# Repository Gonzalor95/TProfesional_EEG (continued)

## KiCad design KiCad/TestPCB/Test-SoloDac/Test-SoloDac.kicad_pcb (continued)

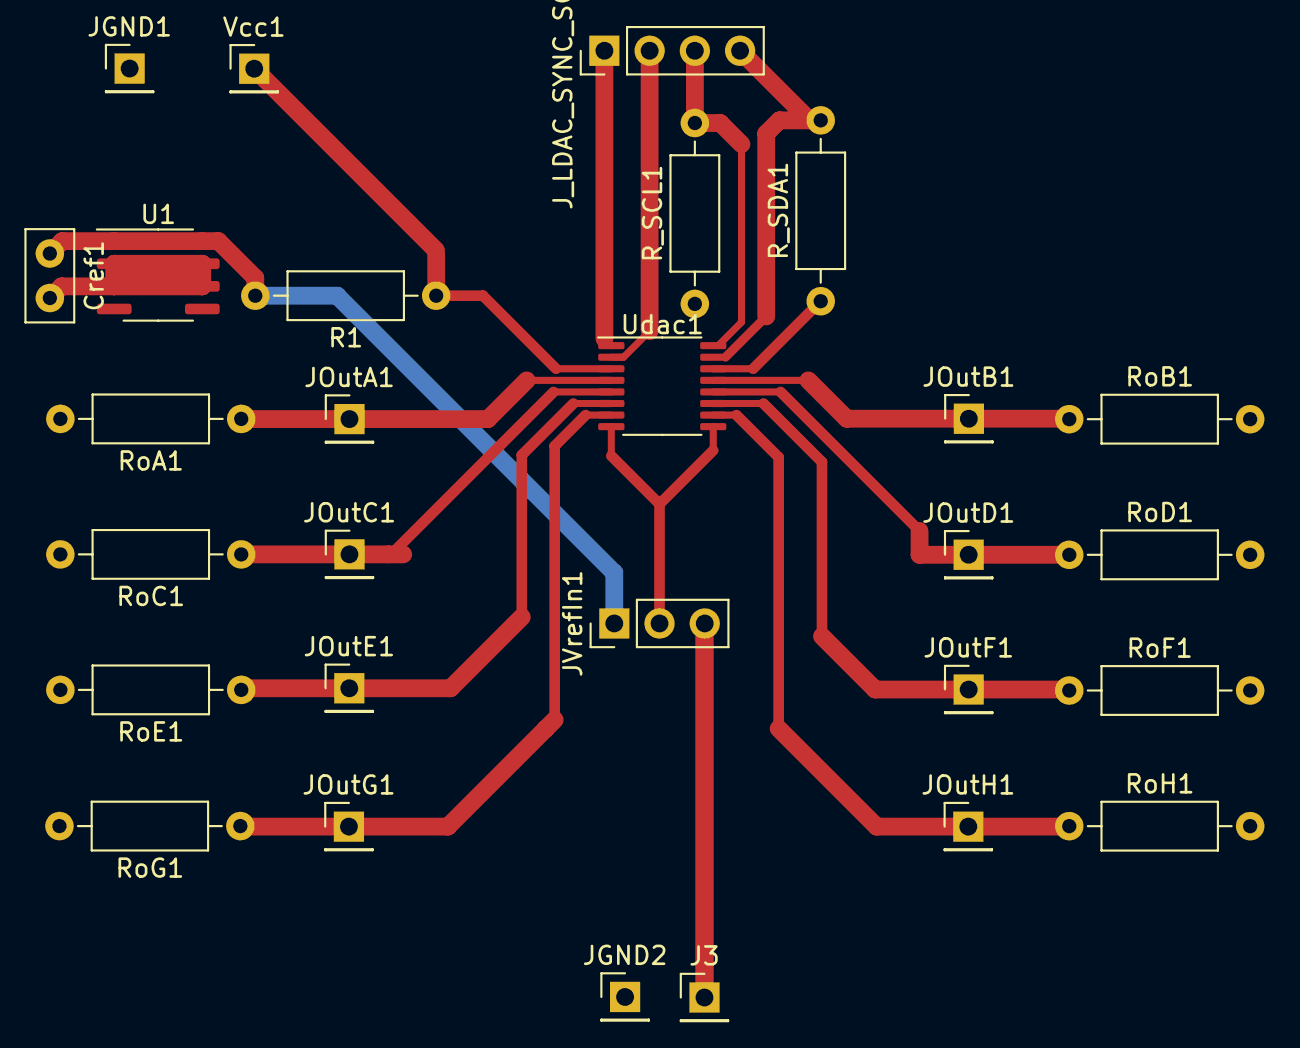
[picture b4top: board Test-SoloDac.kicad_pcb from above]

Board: 2 copper layers, 28 parts (0 on the bottom side), 17 nets.

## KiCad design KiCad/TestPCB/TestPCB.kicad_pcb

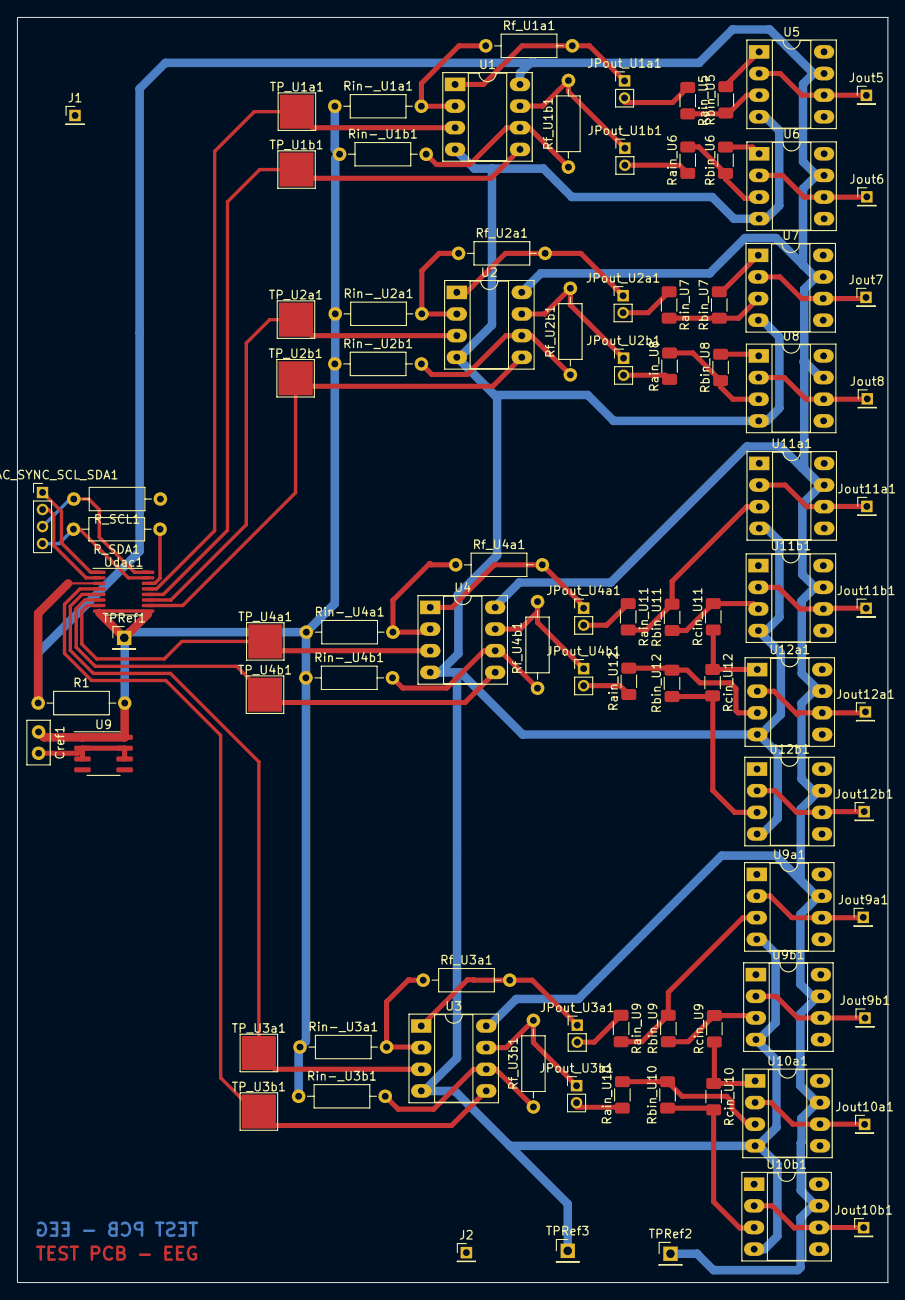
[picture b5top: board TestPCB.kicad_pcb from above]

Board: 2 copper layers, 102.1 x 148.4 mm, 92 parts (0 on the bottom side), 64 nets.

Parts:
Cref1: 100n; C_Disc_D5.0mm_W2.5mm_P2.50mm
J1, J2: Conn_01x01_Male; PinHeader_1x01_P2.00mm_Vertical
JPout_U1a1, JPout_U1b1, JPout_U2a1, JPout_U2b1, JPout_U3a1, JPout_U3b1, JPout_U4a1, JPout_U4b1: Jumper_2_Bridged; PinHeader_1x02_P2.00mm_Vertical
J_LDAC_SYNC_SCL_SDA1: Conn_01x04_Male; PinHeader_1x04_P2.00mm_Vertical
Jout5, Jout6, Jout7, Jout8, Jout9a1, Jout9b1, Jout10a1, Jout10b1, Jout11a1, Jout11b1, Jout12a1, Jout12b1: Conn_01x01_Male; PinHeader_1x01_P2.00mm_Vertical
R1: R; R_Axial_DIN0207_L6.3mm_D2.5mm_P10.16mm_Horizontal
R_SCL1: 10k; R_Axial_DIN0207_L6.3mm_D2.5mm_P10.16mm_Horizontal
R_SDA1: 10k; R_Axial_DIN0207_L6.3mm_D2.5mm_P10.16mm_Horizontal
Rain_U5, Rain_U6, Rain_U7, Rain_U8: 1meg; R_1206_3216Metric_Pad1.30x1.75mm_HandSolder
Rain_U9, Rain_U10, Rain_U11, Rain_U12: 500k; R_1206_3216Metric_Pad1.30x1.75mm_HandSolder
Rbin_U5, Rbin_U6, Rbin_U7, Rbin_U8, Rbin_U9, Rbin_U10, Rbin_U11, Rbin_U12: 10; R_1206_3216Metric_Pad1.30x1.75mm_HandSolder
Rcin_U9, Rcin_U10, Rcin_U11, Rcin_U12: 500k; R_1206_3216Metric_Pad1.30x1.75mm_HandSolder
Rf_U1a1, Rf_U1b1, Rf_U2a1, Rf_U2b1, Rf_U3a1, Rf_U3b1, Rf_U4a1, Rf_U4b1: 10k; R_Axial_DIN0207_L6.3mm_D2.5mm_P10.16mm_Horizontal
Rin-_U1a1, Rin-_U1b1, Rin-_U2a1, Rin-_U2b1, Rin-_U3a1, Rin-_U3b1, Rin-_U4a1, Rin-_U4b1: 10k; R_Axial_DIN0207_L6.3mm_D2.5mm_P10.16mm_Horizontal
TPRef1, TPRef2, TPRef3: Conn_01x01_Male; PinHeader_1x01_P2.54mm_Vertical
TP_U1a1, TP_U1b1, TP_U2a1, TP_U2b1, TP_U3a1, TP_U3b1, TP_U4a1, TP_U4b1: TestPoint; TestPoint_Pad_4.0x4.0mm
U1, U2, U3, U4: MC33078; DIP-8_W7.62mm_Socket_LongPads
U5, U6, U7, U8, U9a1, U9b1, U10a1, U10b1, U11a1, U11b1, U12a1, U12b1: OP07; DIP-8_W7.62mm_Socket_LongPads
U9: TL431D; SOIC-8_3.9x4.9mm_P1.27mm
Udac1: DAC5578xPW; TSSOP-16_4.4x5mm_P0.65mm

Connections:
+2V5: Cref1.1, R1.2, Rin-_U1a1.1, Rin-_U1b1.1, Rin-_U2a1.1, Rin-_U2b1.1, Rin-_U3a1.1, Rin-_U3b1.1, Rin-_U4a1.1, Rin-_U4b1.1, TPRef1.1, U9.1 (K), U9.8 (REF), Udac1.8 (VREFIN), Udac1.9 (~CLR)
+5V: R1.1, TPRef2.1, U1.8 (V+), U2.8 (V+), U3.8 (V+), U4.8 (V+), U5.7 (V+), U6.7 (V+), U7.7 (V+), U8.7 (V+), U9a1.7 (V+), U9b1.7 (V+), U10a1.7 (V+), U10b1.7 (V+), U11a1.7 (V+), U11b1.7 (V+), U12a1.7 (V+), U12b1.7 (V+), Udac1.3 (AVDD)
-5V: TPRef3.1, U1.4 (V-), U2.4 (V-), U3.4 (V-), U4.4 (V-), U5.4 (V-), U6.4 (V-), U7.4 (V-), U8.4 (V-), U9a1.4 (V-), U9b1.4 (V-), U10a1.4 (V-), U10b1.4 (V-), U11a1.4 (V-), U11b1.4 (V-), U12a1.4 (V-), U12b1.4 (V-)
GND: Cref1.2, J1.1, J2.1, R_SCL1.1, R_SDA1.1, Rbin_U5.2, Rbin_U6.2, Rbin_U7.2, Rbin_U8.2, Rcin_U9.1, Rcin_U10.1, Rcin_U11.1, Rcin_U12.1, U5.1 (VOS), U5.8 (VOS), U6.1 (VOS), U6.8 (VOS), U7.1 (VOS), U7.8 (VOS), U8.1 (VOS), U8.8 (VOS), U9.2 (A), U9.3 (A), U9.6 (A), U9.7 (A), U9a1.1 (VOS), U9a1.8 (VOS), U9b1.1 (VOS), U9b1.8 (VOS), U10a1.1 (VOS), U10a1.8 (VOS), U10b1.1 (VOS), U10b1.8 (VOS), U11a1.1 (VOS), U11a1.8 (VOS), U11b1.1 (VOS), U11b1.8 (VOS), U12a1.1 (VOS), U12a1.8 (VOS), U12b1.1 (VOS), U12b1.8 (VOS), Udac1.14 (GND)
unnamed: JPout_U1a1.1 (A), Rf_U1a1.2, U1.1
unnamed: JPout_U1a1.2 (B), Rain_U5.1
unnamed: JPout_U1b1.1 (A), Rf_U1b1.2, U1.7
unnamed: JPout_U1b1.2 (B), Rain_U6.1
unnamed: JPout_U2a1.1 (A), Rf_U2a1.2, U2.1
unnamed: JPout_U2a1.2 (B), Rain_U7.1
unnamed: JPout_U2b1.1 (A), Rf_U2b1.2, U2.7
unnamed: JPout_U2b1.2 (B), Rain_U8.1
unnamed: JPout_U3a1.1 (A), Rf_U3a1.2, U3.1
unnamed: JPout_U3a1.2 (B), Rain_U9.1
unnamed: JPout_U3b1.1 (A), Rf_U3b1.2, U3.7
unnamed: JPout_U3b1.2 (B), Rain_U10.1
unnamed: JPout_U4a1.1 (A), Rf_U4a1.2, U4.1
unnamed: JPout_U4a1.2 (B), Rain_U11.1
unnamed: JPout_U4b1.1 (A), Rf_U4b1.2, U4.7
unnamed: JPout_U4b1.2 (B), Rain_U12.1
unnamed: J_LDAC_SYNC_SCL_SDA1.1, Udac1.1 (~LDAC)
unnamed: J_LDAC_SYNC_SCL_SDA1.2, Udac1.2 (ADDR0)
unnamed: J_LDAC_SYNC_SCL_SDA1.3, R_SCL1.2, Udac1.16 (SCL)
unnamed: J_LDAC_SYNC_SCL_SDA1.4, R_SDA1.2, Udac1.15 (SDA)
unnamed: Jout5.1, U5.2 (-), U5.6
unnamed: Jout6.1, U6.2 (-), U6.6
unnamed: Jout7.1, U7.2 (-), U7.6
unnamed: Jout8.1, U8.2 (-), U8.6
unnamed: Jout9a1.1, U9a1.2 (-), U9a1.6
unnamed: Jout9b1.1, U9b1.2 (-), U9b1.6
unnamed: Jout10a1.1, U10a1.2 (-), U10a1.6
unnamed: Jout10b1.1, U10b1.2 (-), U10b1.6
unnamed: Jout11a1.1, U11a1.2 (-), U11a1.6
unnamed: Jout11b1.1, U11b1.2 (-), U11b1.6
unnamed: Jout12a1.1, U12a1.2 (-), U12a1.6
unnamed: Jout12b1.1, U12b1.2 (-), U12b1.6
unnamed: Rain_U5.2, Rbin_U5.1, U5.3 (+)
unnamed: Rain_U6.2, Rbin_U6.1, U6.3 (+)
unnamed: Rain_U7.2, Rbin_U7.1, U7.3 (+)
unnamed: Rain_U8.2, Rbin_U8.1, U8.3 (+)
unnamed: Rain_U9.2, Rbin_U9.2, U9a1.3 (+)
unnamed: Rain_U10.2, Rbin_U10.2, U10a1.3 (+)
unnamed: Rain_U11.2, Rbin_U11.2, U11a1.3 (+)
unnamed: Rain_U12.2, Rbin_U12.2, U12a1.3 (+)
unnamed: Rbin_U9.1, Rcin_U9.2, U9b1.3 (+)
unnamed: Rbin_U10.1, Rcin_U10.2, U10b1.3 (+)
unnamed: Rbin_U11.1, Rcin_U11.2, U11b1.3 (+)
unnamed: Rbin_U12.1, Rcin_U12.2, U12b1.3 (+)
unnamed: Rf_U1a1.1, Rin-_U1a1.2, U1.2 (-)
unnamed: Rf_U1b1.1, Rin-_U1b1.2, U1.6 (-)
unnamed: Rf_U2a1.1, Rin-_U2a1.2, U2.2 (-)
unnamed: Rf_U2b1.1, Rin-_U2b1.2, U2.6 (-)
unnamed: Rf_U3a1.1, Rin-_U3a1.2, U3.2 (-)
unnamed: Rf_U3b1.1, Rin-_U3b1.2, U3.6 (-)
unnamed: Rf_U4a1.1, Rin-_U4a1.2, U4.2 (-)
unnamed: Rf_U4b1.1, Rin-_U4b1.2, U4.6 (-)
unnamed: TP_U1a1.1, U1.3 (+), Udac1.13 (VOUTB)
unnamed: TP_U1b1.1, U1.5 (+), Udac1.12 (VOUTD)
unnamed: TP_U2a1.1, U2.3 (+), Udac1.11 (VOUTF)
unnamed: TP_U2b1.1, U2.5 (+), Udac1.10 (VOUTH)
unnamed: TP_U3a1.1, U3.3 (+), Udac1.5 (VOUTC)
unnamed: TP_U3b1.1, U3.5 (+), Udac1.4 (VOUTA)
unnamed: TP_U4a1.1, U4.3 (+), Udac1.7 (VOUTG)
unnamed: TP_U4b1.1, U4.5 (+), Udac1.6 (VOUTE)

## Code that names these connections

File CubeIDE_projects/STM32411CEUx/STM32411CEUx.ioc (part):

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Mcu.Name=STM32F411C(C-E)Ux
Mcu.Package=UFQFPN48
Mcu.UserName=STM32F411CEUx
PA1.Mode=TX_Only_Simplex_Unidirect_Master
PA1.Signal=SPI4_MOSI
PA15.Mode=NSS_Signal_Hard_Output
PA15.Signal=SPI3_NSS
PA4.Mode=NSS_Signal_Hard_Output
PA4.Signal=SPI1_NSS
PA5.Mode=TX_Only_Simplex_Unidirect_Master
PA5.Signal=SPI1_SCK
PA7.Mode=TX_Only_Simplex_Unidirect_Master
PA7.Signal=SPI1_MOSI
PB10.Mode=TX_Only_Simplex_Unidirect_Master
PB10.Signal=SPI2_SCK
PB12.Mode=NSS_Signal_Hard_Output
PB12.Signal=SPI4_NSS
PB13.Mode=TX_Only_Simplex_Unidirect_Master
PB13.Signal=SPI4_SCK
PB15.Mode=TX_Only_Simplex_Unidirect_Master
PB15.Signal=SPI2_MOSI
PB3.Mode=TX_Only_Simplex_Unidirect_Master
PB3.Signal=SPI3_SCK
PB5.Mode=TX_Only_Simplex_Unidirect_Master
PB5.Signal=SPI3_MOSI
PB9.Mode=NSS_Signal_Hard_Output
PB9.Signal=SPI2_NSS
RCC.HSE_VALUE=25000000
RCC.SYSCLKFreq_VALUE=16000000
board=custom

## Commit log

2021-09-02 Create edflibc.zip
    Libreria en C para leer archivos edf
2021-09-22 Adding CubeIDE and Proteus projects
2021-09-22 Re-generated deleted USER CODE flags
2021-09-22 testing
2021-09-23 CubeIDE con stm32f103c6 + proteus
2021-09-25 Agrego codigo de prueba SPI
2021-09-25 Transmision SPI debugger exitosa
2021-09-25 Hice mi branch xd
2021-09-30 Subo lo que probe de I2C
2021-10-05 Agrego proyecto proteus
2021-10-05 I2C try
2021-10-07 set test with DAC
2021-10-07 SPI con DAC
2021-10-13 Working SPI with DAC
2021-10-19 SPI example
2021-10-21 Ejemplos de codigos
2021-11-29 Adding Python EDF app
2021-11-29 Adding selected channels parsing method
2021-12-12 Adding pyserial test and BluePill config
2021-12-15 Adding method to get available COM ports
2021-12-15 Fixed digital signal not in order
2021-12-15 Further development
2021-12-18 Windows serial parser, bugfixes
2021-12-18 Unified serial comm searcher methods
2021-12-20 Adding STM32 CubeIDE USB test workspace
2022-01-29 Atenuador draft
2022-02-12 Modularized, error fixes
2022-02-12 Moved two methods to utils
2022-02-12 Major changes
2022-02-21 WIP: Progress with the welcome screen
2022-02-28 Finished welcome screen
2022-02-28 Fixing plot axis
2022-02-28 Method documentation
2022-03-09 Draft diseño de Filtro y Atenuador
2022-03-13 Adding simplified filters
2022-03-13 WIP: Added test signals
2022-03-13 WIP: test pcb
2022-03-14 Change Filter location
2022-03-19 Sacamos Filtro del atenuador
2022-03-19 Esquematico spice con atenuador diferencial
2022-03-26 progress
2022-03-26 Actualizado el kicad
2022-03-27 Linearility check
2022-04-03 Agregadas las versiones a los modulos necesarios en el requirements.txt
2022-04-03 PCB UPDATE
2022-04-03 Finished requirements.txt
2022-04-14 Changing double slider
2022-04-14 WIP: PCB
2022-04-14 WIP PCB
2022-04-17 WIP: Adding channels browser
2022-05-01 IDE changes
2022-05-01 Set configuration for MC_Program
2022-05-03 Adding in-EEG & out-DACs LTSpice test
2022-05-03 Ordening DAC-EEG interface simulation
2022-05-14 Adding alternative output test
2022-05-14 Pushing Kicad Project
2022-05-21 Schematic re-accommodating
2022-05-21 component naming and some footprints
2022-05-21 schematic done, mock footprints assigned
2022-05-22 PCB progress, our outputs done
2022-05-22 First PCB run done
2022-05-22 Added GND pins
2022-06-04 finished desing
2022-06-04 power repositioning
2022-06-05 First set up on MC_Program
2022-06-07 board manufacturing changes
2022-06-14 Envio de Senoidal - Prueba
2022-06-15 Refactor: sine wave test function and libraries
2022-06-20 finished test sine wave for particular DAC and channel
2022-06-20 added function for test Sin() in array of DACs on all channels
2022-06-21 Added USB communication test
2022-06-28 Tested USB receive variable
2022-06-28 Adding Send data functions
2022-07-06 Fixing PCB design
2022-07-07 Creating simple function to send data
2022-08-01 Proyecto de KiCAD para el PCB con el DAC unicamente
2022-08-02 Removidos los pads. Agregados pines y jumpers
2022-08-04 Pistas mas gruesas. Pista para 3,3V
2022-08-22 zip con TP de tercero Probado
2022-08-24 Prueba 1
2022-08-26 codigo para stm32 funcionando
2022-08-31 envio de dato modularizado y envio de cuadrada
2022-08-31 file para hacer traduccion de bytes en C
2022-08-31 nuevos EEG_Simulation.h y .c files. Uso del Error_Handler()
2022-09-03 add get channel mask
2022-09-03 Added DAC handler
2022-09-03 add triangular wave function. Still not working
2022-09-04 Agregamos triangular con frequency step
2022-09-05 Adding black pill kicad models, pcb draft
2022-09-10 progress - almost done
2022-09-12 progress - done
2022-09-21 Test USB
2022-09-21 sync pin and power outputs
2022-09-22 triangular por USB
2022-09-25 Change in spi
2022-11-07 Added config words
2022-11-16 test with 2 dacs
2022-11-16 Fixind DRC checker error
2022-11-16 Board2 first commit
2022-11-18 added enum protocol_words
2022-11-18 Adding ground to output pins
2022-11-21 un monton
2022-11-21 Working
2022-11-27 added LDAC functions and config settings
2022-12-04 fixed erros in MC_program
2022-12-30 WORKING - Tren de Pulsos en DAC_B
2023-01-03 fixed warning
2023-01-03 Resolved issue with config init
2023-01-03 enable init LDAC settings
2023-01-03 Working LDAC with USB communication included
2023-01-15 Adding -5V circuit
2023-01-18 init PC_to_MC module
2023-01-18 Class Comm_PC_to_MC
2023-01-18 Rename file to match Class name
2023-01-18 declaring some vars
2023-02-09 test for commPCtoMC module
2023-02-09 renaming module for comm PC to MC
2023-02-09 init tests for commPCtoMC
2023-02-09 creating commPCtoMC object
2023-02-09 adding plot misc test functions
2023-02-11 adding signalGenerator.py
2023-02-15 comment Juan test waves
2023-02-17 Major refactor
2023-02-21 Run methods to get the signals
2023-02-22 Adding digital testing signal
2023-02-22 Adding some signal preprocessing
2023-02-22 Adding run algorithm
2023-02-23 Changed sending logic
2023-02-23 Fixing channel selection bug
2023-02-23 Re-ordering welcome screen buttons
2023-02-23 some quick tests
2023-02-23 added new requirement
2023-02-23 minor patches for fixes. Must review
2023-03-11 adding mt3608 circuit
2023-03-11 fixed hardcoded serial port
2023-03-11 Adding battery circuit
2023-03-11 -5 generator circuit
2023-03-11 added some output models
2023-03-12 fixed buffer size in MC program
2023-03-15 Adding rest of output opamps
2023-03-19 Removing old stuff
2023-03-21 Code changes
2023-03-21 changing condition to flag
2023-03-21 Resetting buffer
2023-03-21 Changing flag to int
2023-03-21 wip: optimization
2023-03-22 wip: refactor
2023-03-22 Refactor done
2023-03-22 USB transmission fix
2023-03-23 fixes to work
2023-03-24 Moving logic to usb receive
2023-03-26 fixes, working
2023-03-26 fix typo
2023-03-26 adding timit util funciton
2023-04-02 Configuration to use sample rate in STM32 code - WIP: Need to implement queue
2023-04-03 Sample rate managed by MCU. Min sample time 1ms
2023-04-03 no default 1ms in Delay + quick_serial_test.py with timit
2023-04-03 fixed sample_rate send
2023-04-15 Added ldac_trigger to bytes_pacakge. Increased package size for USBD_CDC_ReceivePackage
2023-04-15 process increased buffer size correctly
2023-05-08 first implementation of queue
2023-05-11 Stop interrupt from USB data receive - WIP
2023-05-12 board2 progress
2023-05-30 DO NOT DELETE - readding test functions
2023-05-30 adding RTOS with test function - OK
2023-05-31 USB + RTOS (WIP)
2023-05-31 WIP: USB + RTOS + queue (partially working)
2023-06-07 Added processed edf signal.Add channel_amount configuration pkg
2023-06-08 osdelay addition - WIP
2023-06-08 minor comment
2023-06-09 Adding second layour
2023-06-11 change config to be send inmmediatly when it receives a message
2023-06-11 add config simulation channel amount
2023-06-11 Handle A1/A2 channels. Remove LDAC trigger from bytes_packages. Use os.path to make program more OS-agnostic
2023-06-11 setting max device value
2023-06-17 board2-layout2 complete
2023-06-17 setting timer
2023-06-20 adding timer as interrupt
2023-06-24 Change pin header to female
2023-06-25 RTOS + extra TIM2 for LDAC - Will hold this implementation
2023-06-25 Adding jumpers, checking GND
2023-06-25 re-routing power
2023-06-25 power connection
2023-06-27 working TIM2
2023-06-29 adding extra timer
2023-06-29 integrate TIM2(SPI send) TIM3(LDAC) and USB
2023-06-29 Adding gnd to pot, cleaning vias and tracks
2023-06-30 changed tim configs + data queue size + discarded channels flush
2023-07-06 correct sampling + correct volts division in PC
2023-07-08 Tidying up serialCommWorker
2023-07-08 Passing device config to all modules
2023-07-08 Tidying up utils
2023-07-08 Tidying up TestingSignals
2023-07-08 Fixing selected time for testing signals
2023-07-08 Tidying up EDFWorker
2023-07-08 Adding try catch and serial timeout
2023-07-08 Fixing edf worker selected sim time
2023-07-08 changed bit_resolution and max_digital
2023-07-13 Some mess in the queues and start-ending condition
2023-07-14 fixed signal transformation to digital
2023-07-16 adding transform to testing signals and EDF worker
2023-07-17 fixed when to reset dacs
2023-07-18 fixed queue error
2023-07-19 round corrected in sample_rate calc
2023-08-19 adding EEG_analysis
2023-08-20 testing cross correlation to adjust signals automatically
2023-08-20 getting the test signal analysis working
2023-08-20 adding commonsample1 edf
2023-08-20 adding commonsample1 test
2023-08-21 adding Sen1Hz test
2023-08-21 Added signal analysis script
2023-08-21 woks pretty well
2023-08-21 Show full correlated signal
2023-08-26 adding SMA filter
2023-08-27 fix wrong merge
2023-08-27 Adding missing requirement
2023-08-27 Modifying GUI elements
2023-08-27 WIP: Adding sample_rate logic
2023-08-28 adding GonzAnalysis and EEGAnalysisUtilities.py
2023-08-28 putting steps on EEG_analysis
2023-08-29 changes in edfworked for variable sample rate
2023-08-29 Disabling sample rate config for testing signals
2023-09-03 push GonzAnalysis
2023-09-04 Reworked GonzAnalysis
2023-09-04 improving gonzAnalysis
2023-09-06 adding freq analysis
2023-09-06 Nachanges
2023-09-12 modifying Pulse and adding inverse Filter
2023-09-12 added freq response in triangular
2023-09-12 adding freq response in triangular + inverse filter (commented)
2023-09-13 adding more samples + analysis of Sen
2023-09-13 Add optimized SMA filtering
2023-09-20 adding Freq Response analysis + some EDFs
2023-09-24 Create README.md with instructions
2023-09-24 adding more analysis
2023-09-30 select best data window
2023-10-01 adding more EDFs
2023-10-01 Agregado analisis de 4 señales promediadas
2023-10-01 Graficos de intervalos
2023-10-02 adding SNR + correct some edfs
2023-10-02 fix up some edfs
2023-10-03 freq_analysis
2023-10-05 check EDFs + crossover file
2023-10-06 add multiple signals for generate_output_signal
2023-10-09 improve Crossover script
2023-10-10 finish up crossover script
2023-10-16 square analysis
2023-10-31 removing leftover comments
2023-11-11 adding extra fiels
2023-11-12 adding freq response interpolation
2023-12-16 code cleaning
2024-02-06 Translating to spanish
2024-02-06 changes in analysis scripts
2024-02-10 Adding run generator script
2024-03-21 error
